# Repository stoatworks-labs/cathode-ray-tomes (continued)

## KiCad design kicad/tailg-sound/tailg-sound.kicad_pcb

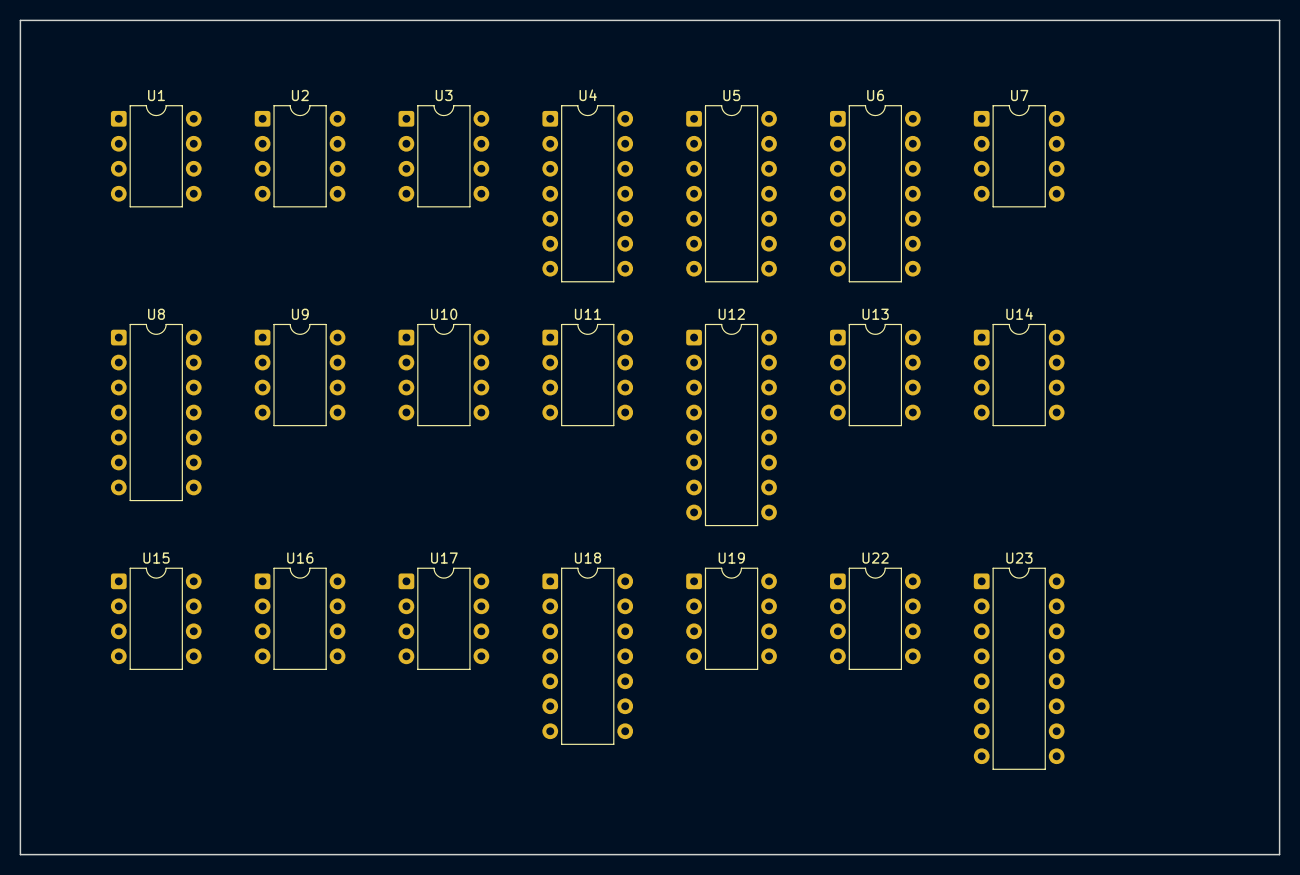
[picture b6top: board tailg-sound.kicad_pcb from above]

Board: 2 copper layers, 128.0 x 84.8 mm, 21 parts (0 on the bottom side), 23 nets, no tracks yet.

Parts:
U1, U2, U3, U7, U9, U11, U19: TL081; DIP-8_W7.62mm
U4: 74LS125; DIP-14_W7.62mm
U5: 7404; DIP-14_W7.62mm
U6: 7406; DIP-14_W7.62mm
U8, U18: 74LS393; DIP-14_W7.62mm
U10, U13, U22: CA3080; DIP-8_W7.62mm
U12: 74LS123; DIP-16_W7.62mm
U14, U15, U16, U17: LM555; DIP-8_W7.62mm
U23: 74LS259; DIP-16_W7.62mm

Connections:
+5V: U4.14, U5.14, U6.14, U8.14, U12.2, U12.3, U12.10, U12.11, U12.16, U14.4, U14.8, U15.4, U15.8, U18.14, U23.15, U23.16
+15V: U2.7, U3.7, U7.7, U9.7, U10.7, U11.7, U13.7, U16.4, U16.8, U17.4, U17.8, U19.7, U22.7
-15V: U1.4, U2.4, U3.4, U7.4, U9.4, U10.4, U11.4, U13.4, U19.4, U22.4
GND: U2.3, U3.3, U4.2, U4.5, U4.7, U5.7, U6.7, U8.7, U9.3, U12.8, U14.1, U15.1, U16.1, U17.1, U18.2, U18.7, U18.12, U19.3, U23.8
unnamed: U14.2, U14.6
unnamed: U15.2, U15.6
unnamed: U16.2, U16.6
unnamed: U17.2, U17.6
unnamed: U4.3, U5.5, U8.12
unnamed: U4.6, U6.3, U8.2
unnamed: U5.2, U8.13
unnamed: U5.4, U8.1
unnamed: U5.6, U6.1
unnamed: U12.1, U23.4
unnamed: U12.9, U23.9
unnamed: U4.10, U12.12
unnamed: U14.3, U18.1
unnamed: U15.3, U18.13
unnamed: U6.5, U23.5
unnamed: U4.4, U23.6
unnamed: U4.13, U23.7
unnamed: U4.1, U23.10
OUTPUT: U10.6, U13.6, U22.6

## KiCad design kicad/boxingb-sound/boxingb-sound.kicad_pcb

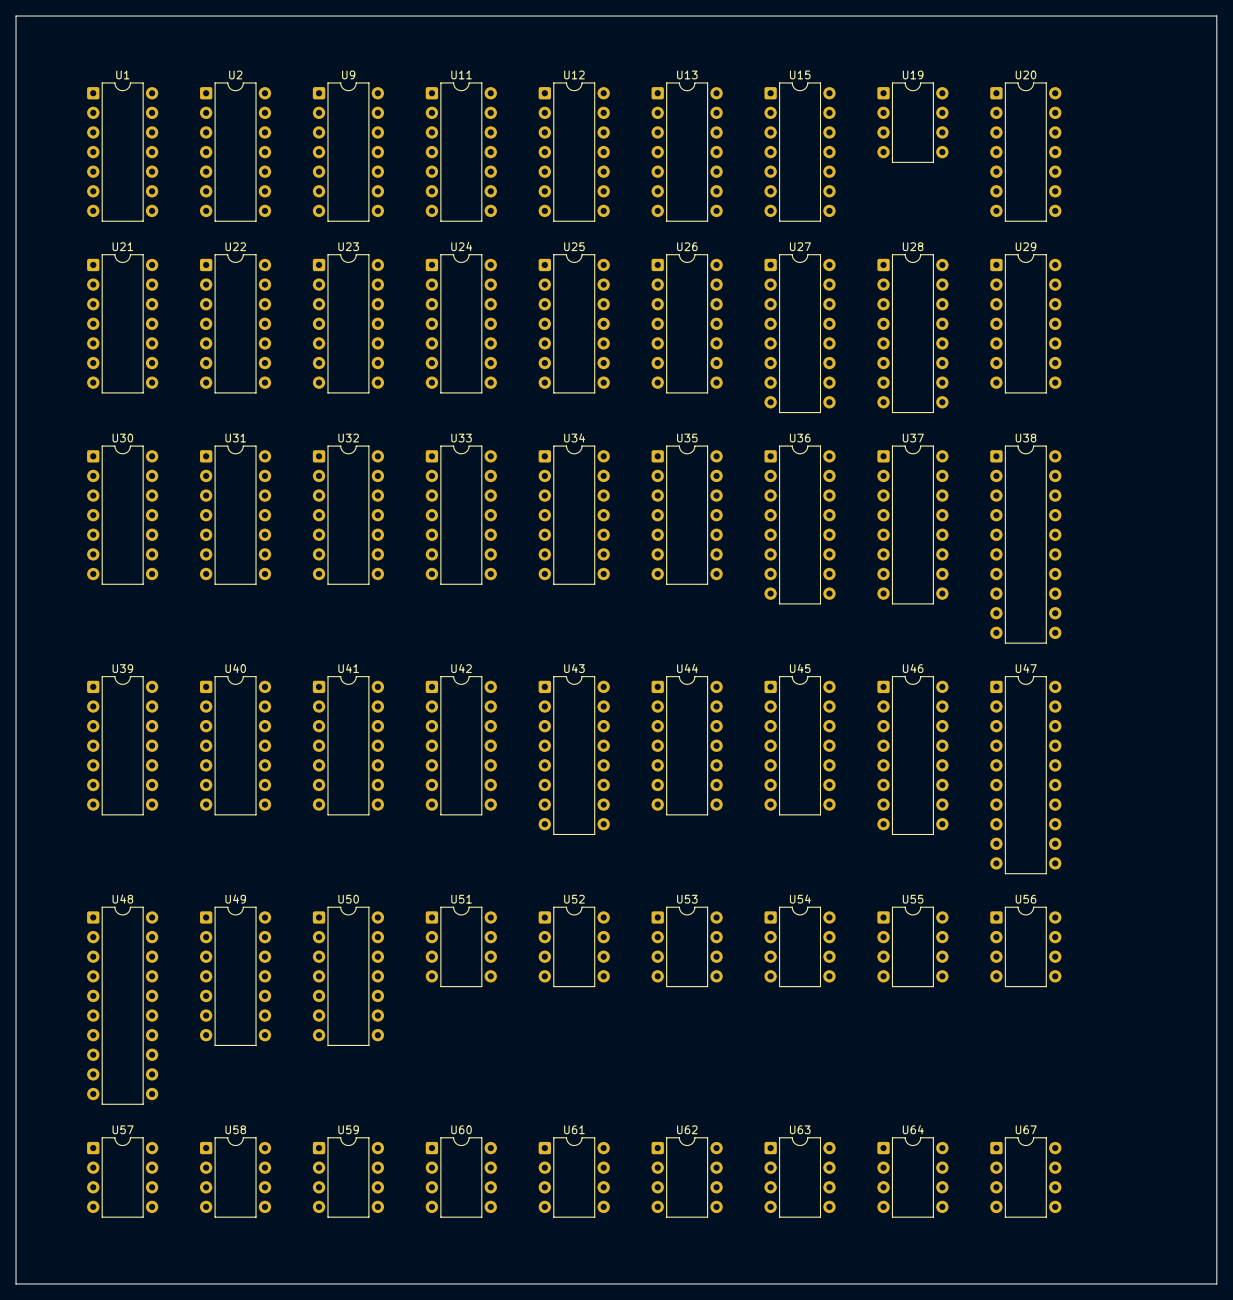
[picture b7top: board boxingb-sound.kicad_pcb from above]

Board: 2 copper layers, 155.5 x 164.2 mm, 54 parts (0 on the bottom side), 120 nets, no tracks yet.

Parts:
U1, U13, U15, U21, U22, U26, U32, U41, U42: 74LS393; DIP-14_W7.62mm
U2: 74S04; DIP-14_W7.62mm
U9, U33, U34: 74LS107; DIP-14_W7.62mm
U11, U39, U49: 74LS164; DIP-14_W7.62mm
U12: 74LS86; DIP-14_W7.62mm
U19, U58: LM555; DIP-8_W7.62mm
U20, U30, U50: 7414; DIP-14_W7.62mm
U23: 74S113; DIP-14_W7.62mm
U24, U25, U29, U44, U45: 74LS74; DIP-14_W7.62mm
U27, U28, U36, U37, U43, U46: 74LS163; DIP-16_W7.62mm
U31: 74LS04; DIP-14_W7.62mm
U35: 74LS02; DIP-14_W7.62mm
U38, U47, U48: 74LS377; DIP-20_W7.62mm
U40: 7406; DIP-14_W7.62mm
U51, U52, U53, U56, U57, U60: LM566; DIP-8_W7.62mm
U54, U55, U63: TL081; DIP-8_W7.62mm
U59, U61, U64, U67: CA3080; DIP-8_W7.62mm
U62: S2688; DIP-8_W7.62mm

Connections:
+5V: U1.14, U2.14, U9.14, U11.14, U12.14, U13.14, U15.14, U19.8, U20.14, U21.14, U22.14, U23.14, U24.14, U25.14, U26.14, U27.16, U28.16, U29.14, U30.14, U31.14, U32.14, U33.14, U34.14, U35.14, U36.16, U37.16, U38.20, U39.14, U40.14, U41.14, U42.14, U43.16, U44.14, U45.14, U46.16, U47.20, U48.20, U49.14, U50.14, U58.4, U58.8
+15V: U51.8, U52.8, U53.8, U54.7, U55.7, U56.8, U57.8, U59.7, U60.8, U61.7, U63.7, U64.7, U67.7
-15V: U54.4, U55.4, U59.4, U61.4, U63.4, U64.4, U67.4
ACLK_M: U28.2, U29.6
ACLK_P: U29.5, U29.12
BCLK_M: U24.11, U29.2, U29.8
BCLK_P: U26.1, U27.2, U29.9
BEETLE_ON_SCREEN_M: U22.2, U31.1, U47.19
BLOAD_M: U24.8, U27.9, U28.9
BUG_DYING_M: U31.3, U42.12, U47.16
BUG_PUSHING_A_P: U31.9, U47.12
BUG_PUSHING_B_P: U31.11, U47.15
CANNON_M: U13.2, U48.5
CHIRPING_BIRDS_M: U41.12, U47.6
CS: U55.3, U59.6, U61.6, U64.6, U67.6
DATA_P: U49.1, U50.2
EGG_CRACKING_M: U22.12, U31.13, U47.9
ERRCLR_M: U11.9, U35.1
FS00_P: U37.3, U38.19
FS01_P: U37.4, U38.16
FS02_P: U37.5, U38.15
FS03_P: U37.6, U38.12
FS04_P: U36.3, U38.9
FS05_P: U36.4, U38.6
FS06_P: U36.5, U38.5
FS07_P: U36.6, U38.2
FS08_P: U46.3, U48.19
FS09_P: U46.4, U48.16
FS10_P: U46.5, U48.15
FS11_P: U46.6, U48.12
GND: U1.2, U1.7, U1.12, U2.5, U2.7, U2.9, U2.11, U9.7, U11.7, U12.7, U13.7, U13.12, U15.7, U19.1, U20.7, U21.7, U22.7, U23.7, U24.7, U25.7, U26.2, U26.7, U26.12, U27.3, U27.8, U28.4, U28.5, U28.8, U29.7, U30.7, U31.7, U32.7, U32.12, U33.7, U34.7, U35.7, U36.8, U37.8, U38.1, U38.10, U39.7, U40.7, U41.7, U42.7, U43.4, U43.6, U43.8, U44.7, U45.7, U46.8, U47.1, U47.10, U48.1, U48.10, U49.7, U50.7, U51.1, U52.1, U53.1, U54.3, U56.1, U57.1, U58.1, U60.1, U62.1, U62.2
HIA_P: U24.10, U25.2, U25.4, U25.10, U34.1, U34.4, U34.8, U34.10, U34.11, U34.13, U36.1, U37.1, U39.2, U39.9, U44.1, U44.4, U44.10, U44.13, U45.4, U45.13, U46.1, U49.2, U49.9
HIB_P: U27.1, U27.4, U27.5, U27.6, U27.7, U28.1, U28.3, U28.6, U28.7, U28.10, U29.1, U29.4, U29.10, U29.13
HIC_P: U23.2, U23.3, U23.4, U23.10, U23.11, U23.12, U24.4, U33.1, U33.4, U33.13, U43.1, U43.3, U43.5, U43.7, U43.10
HID_P: U9.8, U9.10, U9.11, U12.10
IN_M: U11.1, U11.2, U12.8
LATCH_CLK_P: U25.3, U30.4
MACLK_M: U25.11, U44.2, U44.8
MACLK_P: U36.2, U44.9, U45.3
MBCLK_M: U15.13, U37.2, U44.6
MBCLK_P: U44.5, U44.12, U45.11, U46.2
MCARRY_P: U25.12, U46.15
MEN_P: U36.7, U37.7, U37.10, U46.7, U48.2
MLATCH_P: U38.11, U45.2, U45.9, U48.11
MLOAD_M: U25.8, U36.9, U37.9, U46.9
MLOAD_P: U25.9, U34.9, U35.8
unnamed: U19.2, U19.6
unnamed: U55.2, U55.6
unnamed: U30.13, U40.8
unnamed: U2.2, U2.13
unnamed: U30.9, U40.12
unnamed: U30.11, U40.10
unnamed: U19.3, U20.1
unnamed: U63.2, U63.6
unnamed: U1.10, U11.8, U32.1
unnamed: U1.6, U1.13
unnamed: U2.12, U23.1
unnamed: U11.4, U12.4
unnamed: U11.5, U12.5
unnamed: U11.6, U12.2
unnamed: U12.9, U12.11, U32.2
unnamed: U12.6, U12.12
unnamed: U12.3, U12.13
unnamed: U9.9, U13.8
unnamed: U15.9, U35.11, U35.12
unnamed: U15.12, U25.6, U35.9
unnamed: U19.4, U31.2
unnamed: U21.2, U31.8
unnamed: U21.12, U31.10
unnamed: U23.5, U23.13
unnamed: U24.2, U43.15
unnamed: U24.6, U33.12, U43.9
unnamed: U24.9, U34.12
unnamed: U24.12, U27.15
unnamed: U25.1, U45.6
unnamed: U26.6, U26.13
unnamed: U27.10, U28.15
unnamed: U9.5, U29.3
unnamed: U9.6, U29.11
unnamed: U30.1, U30.12
unnamed: U30.2, U39.8, U49.8
unnamed: U30.5, U30.8
unnamed: U30.3, U30.10
unnamed: U32.6, U35.2, U35.3
unnamed: U35.10, U45.12
unnamed: U35.13, U45.10
unnamed: U36.10, U37.15
unnamed: U36.15, U46.10
unnamed: U38.3, U39.3
unnamed: U38.4, U39.4
unnamed: U38.7, U39.5
unnamed: U38.8, U39.6
unnamed: U38.13, U39.10
unnamed: U38.14, U39.11
unnamed: U38.17, U39.12
unnamed: U38.18, U39.13
unnamed: U39.1, U47.18, U48.18, U49.13
unnamed: U40.9, U50.12
unnamed: U40.11, U50.10
unnamed: U40.13, U50.4
unnamed: U41.3, U41.13
unnamed: U42.3, U42.13
unnamed: U47.3, U48.3, U49.3
unnamed: U47.4, U48.4, U49.4
unnamed: U47.7, U48.7, U49.5
unnamed: U47.8, U48.8, U49.6
unnamed: U47.13, U48.13, U49.10
unnamed: U47.14, U48.14, U49.11
unnamed: U47.17, U48.17, U49.12
unnamed: U50.1, U50.8
RANDOM_NOISE_P: U11.13, U12.1, U31.5, U41.2
SLATCH_P: U30.6, U47.11
_5MHZ_M: U13.13, U23.8, U24.3
_5MHZ_P: U23.9, U43.2
_227KC_M: U33.2, U44.11
_227KC_P: U33.3, U44.3
_327USEC_P: U26.8, U32.13
_588USEC_P: U1.1, U21.1, U21.13, U34.3
_2616USEC_P: U32.9, U42.2
_5232USEC_P: U32.8, U58.2, U58.6

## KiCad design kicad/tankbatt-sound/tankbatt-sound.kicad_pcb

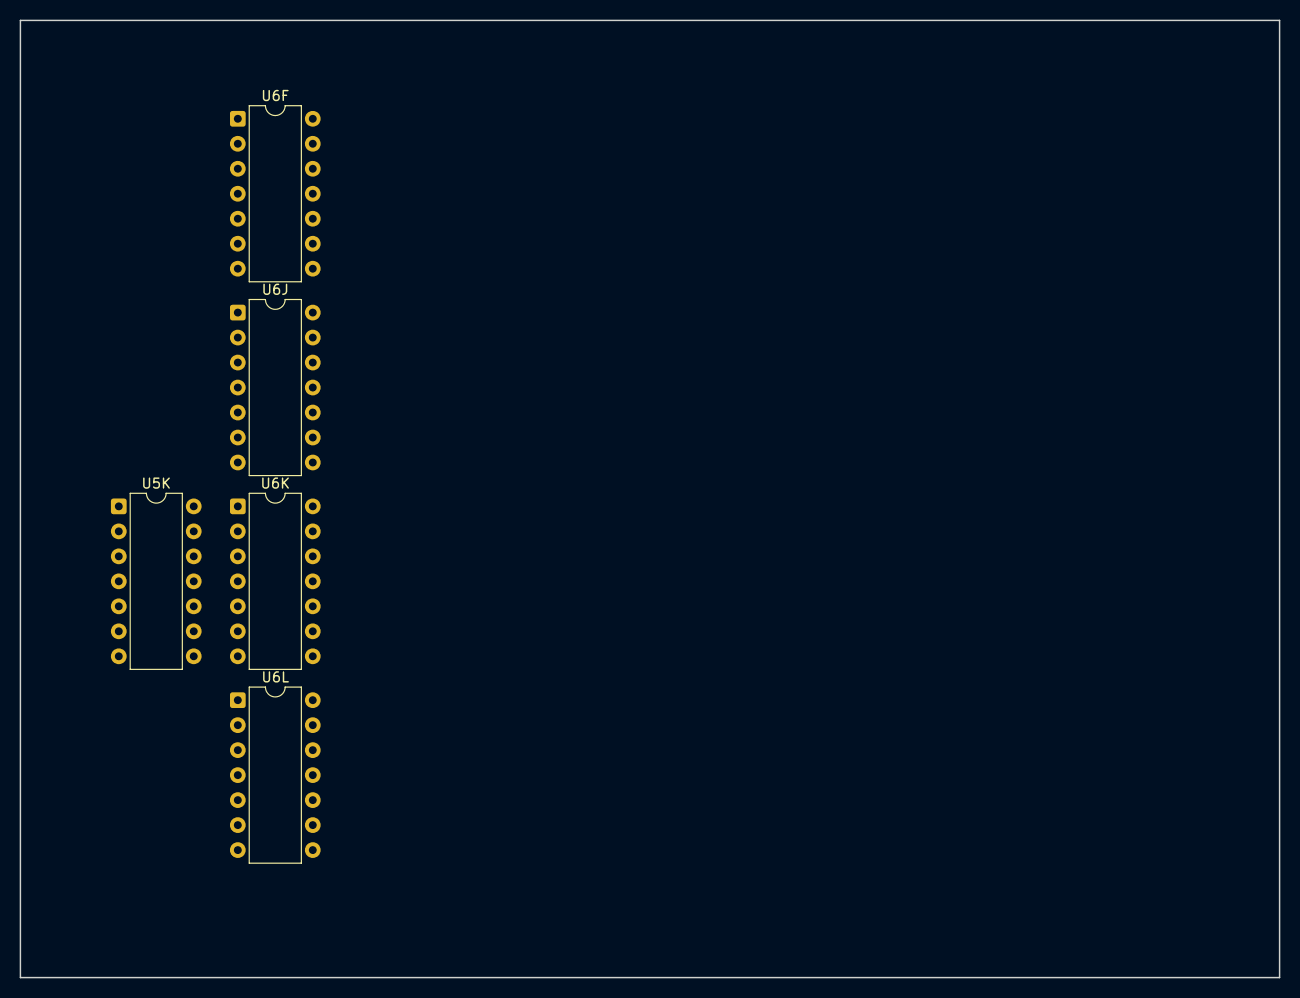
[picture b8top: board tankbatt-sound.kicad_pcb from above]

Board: 2 copper layers, 128.0 x 97.3 mm, 5 parts (0 on the bottom side), 14 nets, no tracks yet.

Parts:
U5K: 7492; DIP-14_W7.62mm
U6F: CD4006; DIP-14_W7.62mm
U6J: LM324; DIP-14_W7.62mm
U6K: 7486; DIP-14_W7.62mm
U6L: CD4066; DIP-14_W7.62mm

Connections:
2V: U6F.3, U6L.1
+5V: U5K.5, U5K.7, U6F.14, U6J.4, U6K.10, U6K.14, U6L.14
GND: U5K.10, U6F.7, U6J.11, U6K.7, U6L.7
unnamed: U6J.3, U6J.10, U6J.12
unnamed: U6J.7, U6K.9
unnamed: U5K.1, U6K.6
unnamed: U5K.8, U6K.13
unnamed: U5K.11, U6K.12
unnamed: U5K.14, U6K.11
unnamed: U6F.1, U6F.12, U6K.1
unnamed: U6F.8, U6K.2
unnamed: U6F.6, U6F.10, U6L.6, U6L.12
unnamed: U6F.5, U6F.13
unnamed: U6K.5, U6K.8
